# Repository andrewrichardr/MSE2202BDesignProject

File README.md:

# TronDesign
MSE2202B Mechatronic Design Repo

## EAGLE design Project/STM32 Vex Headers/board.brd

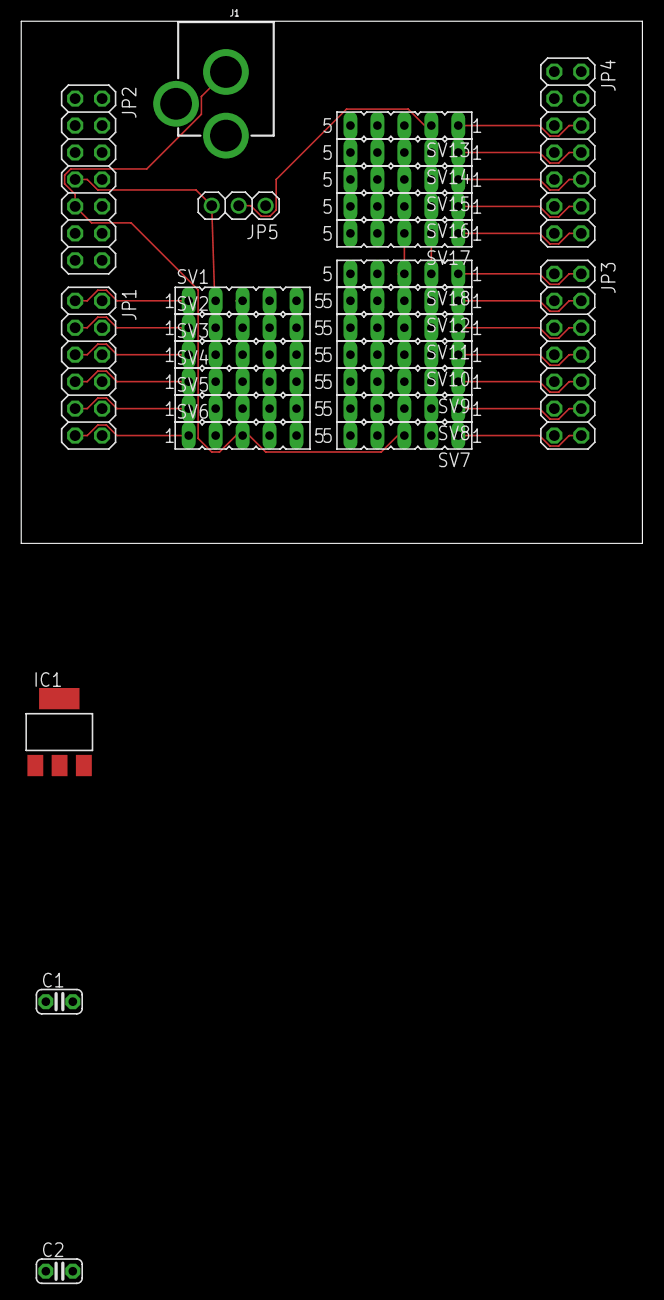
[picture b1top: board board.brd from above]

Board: 2 copper layers, 58.5 x 49.2 mm, 27 parts (0 on the bottom side), 23 nets.

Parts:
C1, C2: C025-024X044
IC1: REG1117; SOT223
J1: POWER_JACK; POWER_JACK_PTH
JP1: 2X06
JP2, JP3, JP4: 2X07
JP5: 1X03
SV1, SV2, SV3, SV4, SV5, SV6, SV7, SV8, SV9, SV10, SV11, SV12, SV13, SV14, SV15, SV16, SV17, SV18: FE05-1

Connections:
unnamed: JP1.1, SV1.1
unnamed: JP3.2, SV18.1
unnamed: JP1.3, SV2.1
unnamed: JP4.14, SV17.1
unnamed: JP1.5, SV3.1
unnamed: JP1.7, SV4.1
unnamed: JP1.9, SV5.1
unnamed: JP1.11, SV6.1
unnamed: JP3.14, SV7.1
unnamed: JP3.12, SV8.1
unnamed: JP3.10, SV9.1
unnamed: JP3.8, SV10.1
unnamed: JP3.6, SV11.1
unnamed: JP3.4, SV12.1
unnamed: JP4.12, SV16.1
unnamed: JP4.10, SV15.1
unnamed: C1.2, C2.2, IC1.1, J1.GND, JP2.9, SV1.3, SV2.3, SV3.3, SV4.3, SV5.3, SV6.3, SV7.3, SV8.3, SV9.3, SV10.3, SV11.3, SV12.3, SV13.3, SV14.3, SV15.3, SV16.3, SV17.3, SV18.3
unnamed: JP5.2, SV7.2, SV8.2, SV9.2, SV10.2, SV11.2, SV12.2, SV13.2, SV14.2, SV15.2, SV16.2, SV17.2, SV18.2
unnamed: JP4.8, SV14.1
unnamed: JP4.6, SV13.1
unnamed: C1.1, IC1.3, J1.PWR
unnamed: JP2.7, JP5.3, SV1.2, SV2.2, SV3.2, SV4.2, SV5.2, SV6.2
unnamed: C2.1, IC1.2, JP5.1

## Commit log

2018-01-18 Lab02
2018-01-19 they all work elegently now
    Please enter the commit message for your changes. Lines starting
2018-01-19 All submitted and accepted
2018-01-23 Lab03 Added
2018-01-23 I2CEncoder Lib added, Will compile with Sublime
2018-01-26 Naive approach to lab 3 added
2018-01-26 Formatting
2018-01-26 House cleaning
2018-01-27 Line following logic functional for a basic loop
2018-01-29 Modular turning functions added
2018-01-30 Added STM32 Guide
2018-01-31 Alan is not in prison
2018-02-01 Streamlined
2018-02-01 Beatrice got fat
2018-02-07 Alan is Anal
2018-02-07 Alan hates Ruizhi
2018-02-08 Alan Cheated on Beatrice
2018-02-15 Racing Edition
2018-03-03 Benchmark Added
2018-03-14 SOLIDWORKS Init
2018-03-14 Test Drive Code Added
2018-03-14 Fan's Code
2018-03-15 Repo Cleanup, Added Eagle Sch for Vex Devices
2018-03-15 Fan's Docs
2018-03-15 Rev 1.0 Prototype Sch Added
2018-03-15 Test Drive Code modified
2018-03-15 Ultrasonic test code added for driving parallel to the wall
2018-03-16 Chassis Gearing Iteration
2018-03-16 Block Diagram Added
2018-03-17 Block Diagram Update
2018-03-17 Cleanup
2018-03-17 Admin
2018-03-17 Pinmuxing required block diagram changes
2018-03-17 Add files via upload
    Still my code
2018-03-17 Code to read IR input
2018-03-18 Added IRQ line for the IR sensor
2018-03-18 File Structuring, Ultrasonic Code added for MSE-Duino-B, Main Code Development Started
2018-03-20 Modified variant.h to enable UART3
2018-03-20 Enabled all UARTx with included boards.txt
2018-03-20 Uarts enabled
2018-03-20 Product CAD update
2018-03-20 Add files via upload
    Intake Parts (Laser Cutting version)
2018-03-21 Added 3rd party libraries for compass / accel
2018-03-22 CAD render + Updates
2018-03-22 DriveCode update
2018-03-22 IR sensor retrieval added
2018-03-22 Updated with drive code
2018-03-23 Final Design CAD added and Chassis started
2018-03-23 Main Robot Class added
2018-03-23 class
2018-03-23 syntax error corrected
2018-03-23 main code\
2018-03-24 minor changes
2018-03-24 cube pickup
2018-03-24 cube pickup..
2018-03-24 small fix
2018-03-24 struct
2018-03-25 logic for putting pyramid over cube
2018-03-25 Repo Cleanup
2018-03-25 NUCLEO-32 Ultrasonic Controller Code added
2018-03-25 FAN's code added back
2018-03-26 fan demo
2018-03-29 Drive Test code iterative update
2018-03-29 CAD and Sensor Test Code
2018-03-29 Main Code work progressed
2018-04-01 testing mods
2018-04-01 Added PID controlled wall follower code to test
2018-04-01 adds new Lift and Claw CAD parts
2018-04-02 should fix Solidworks opening issues
2018-04-02 Block Diag Updated
2018-04-02 Fans code: Added functions and vars for arm and lift positions, cleaned up repo
2018-04-03 last minute cad
2018-04-04 progress
2018-04-06 kjdfsgkjfsdjgksdg
2018-04-07 CADDING PROTOTYPE
2018-04-07 CAD progress
2018-04-08 prototype caD
2018-04-08 Prototype CAD Completed
2018-04-09 Final Design CAD progress
2018-04-10 Final Drawings
2018-04-11 adding new CADded files
2018-04-11 Drawings
2018-04-12 Completed

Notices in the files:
parts and their libraries:
SparkFun-Connectors: Licensing: Creative Commons ShareAlike 4.0 International - https://creativecommons.org/licenses/by-sa/4.0
